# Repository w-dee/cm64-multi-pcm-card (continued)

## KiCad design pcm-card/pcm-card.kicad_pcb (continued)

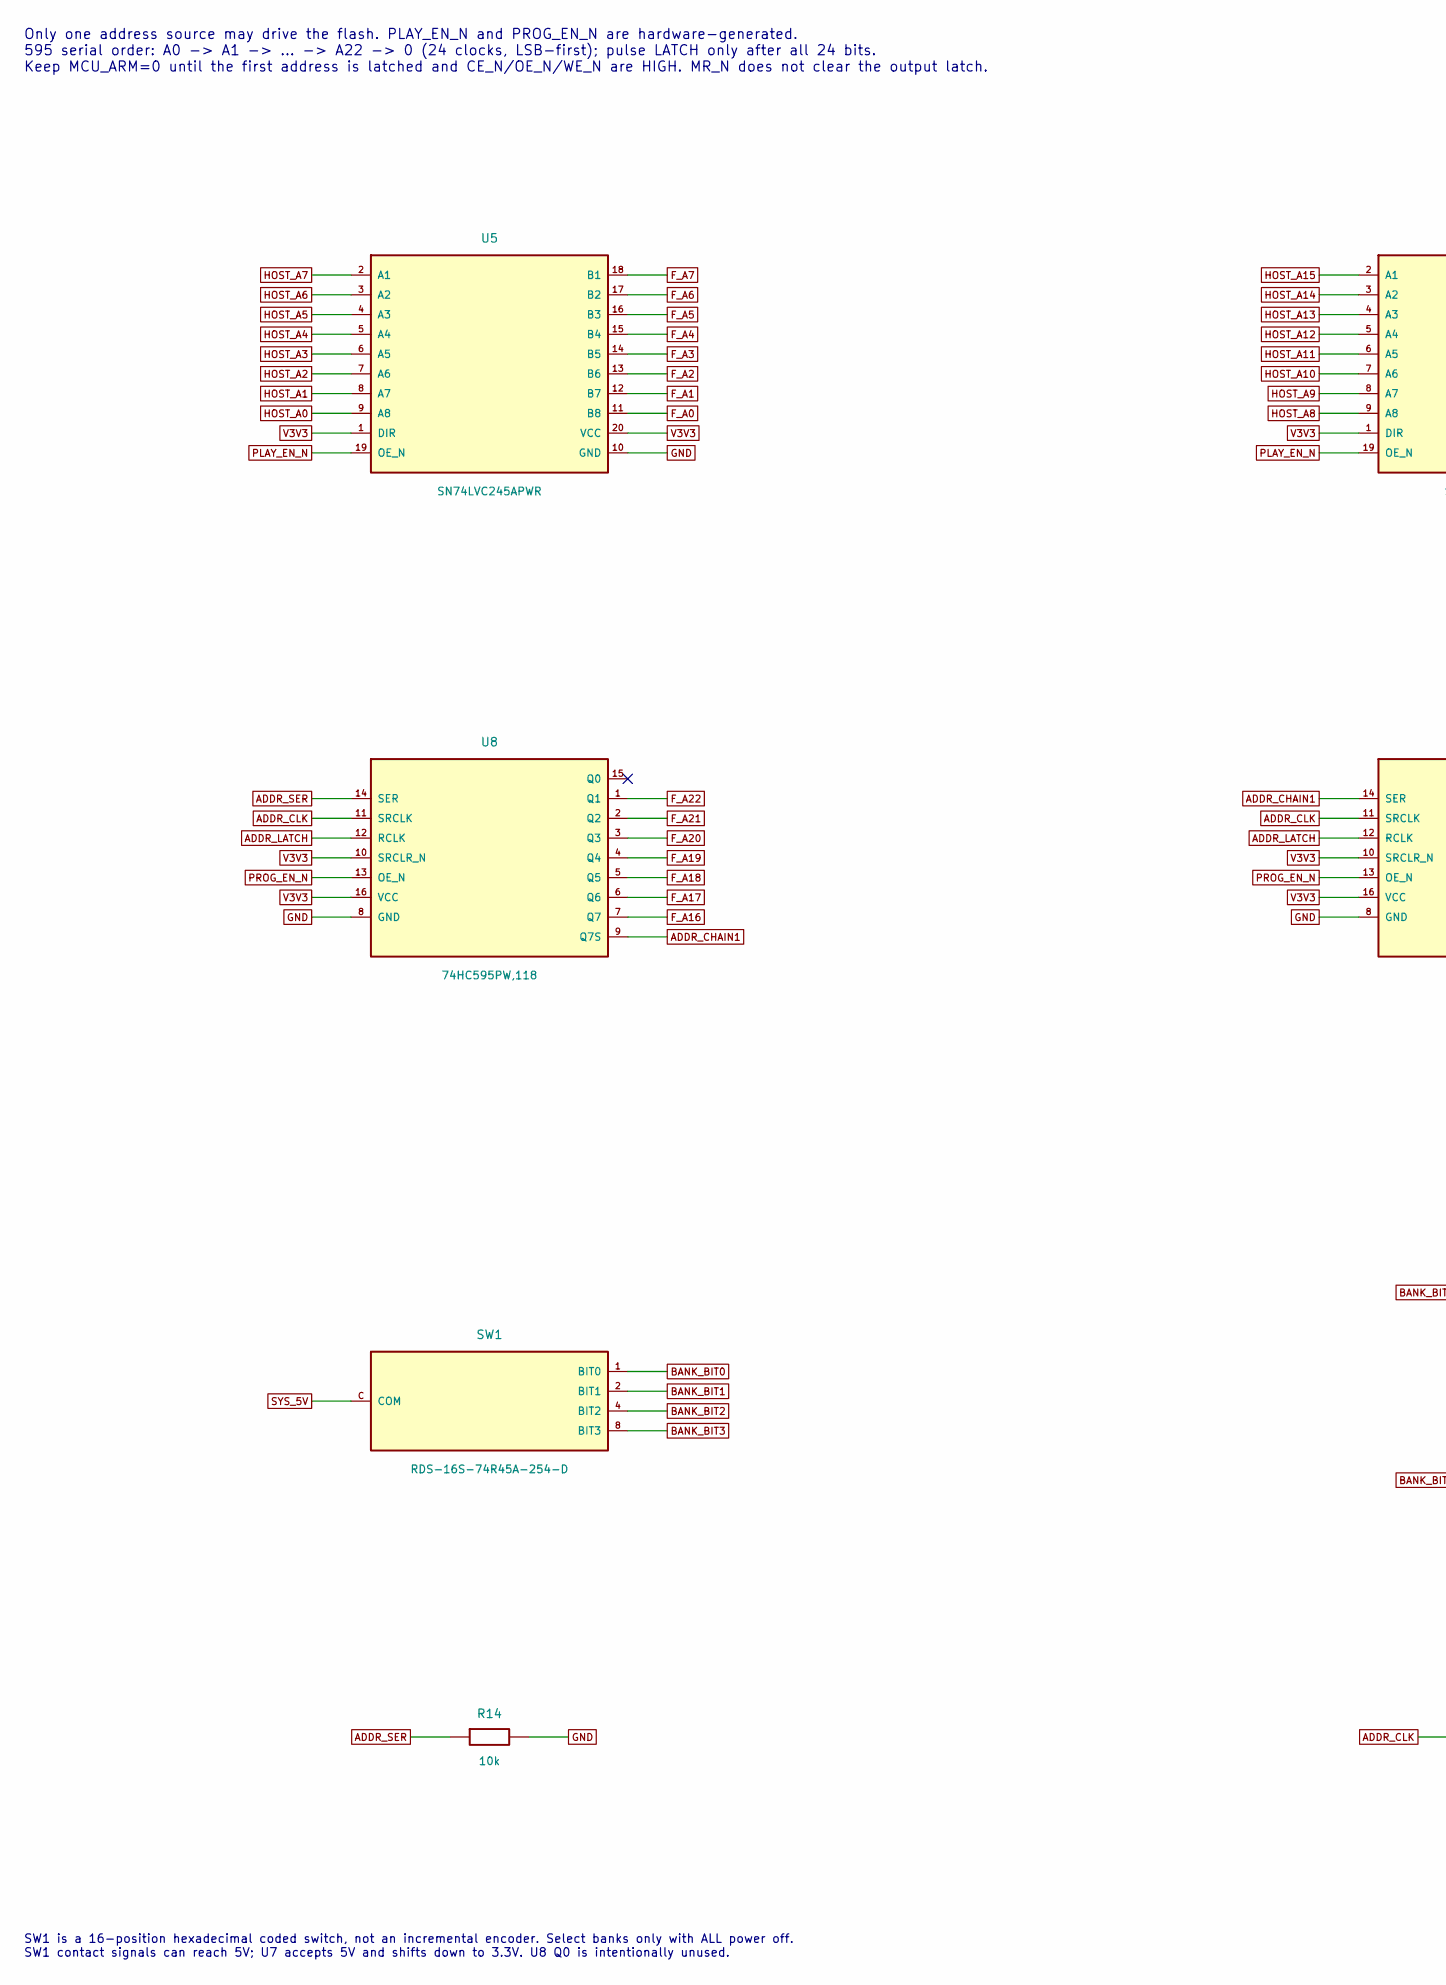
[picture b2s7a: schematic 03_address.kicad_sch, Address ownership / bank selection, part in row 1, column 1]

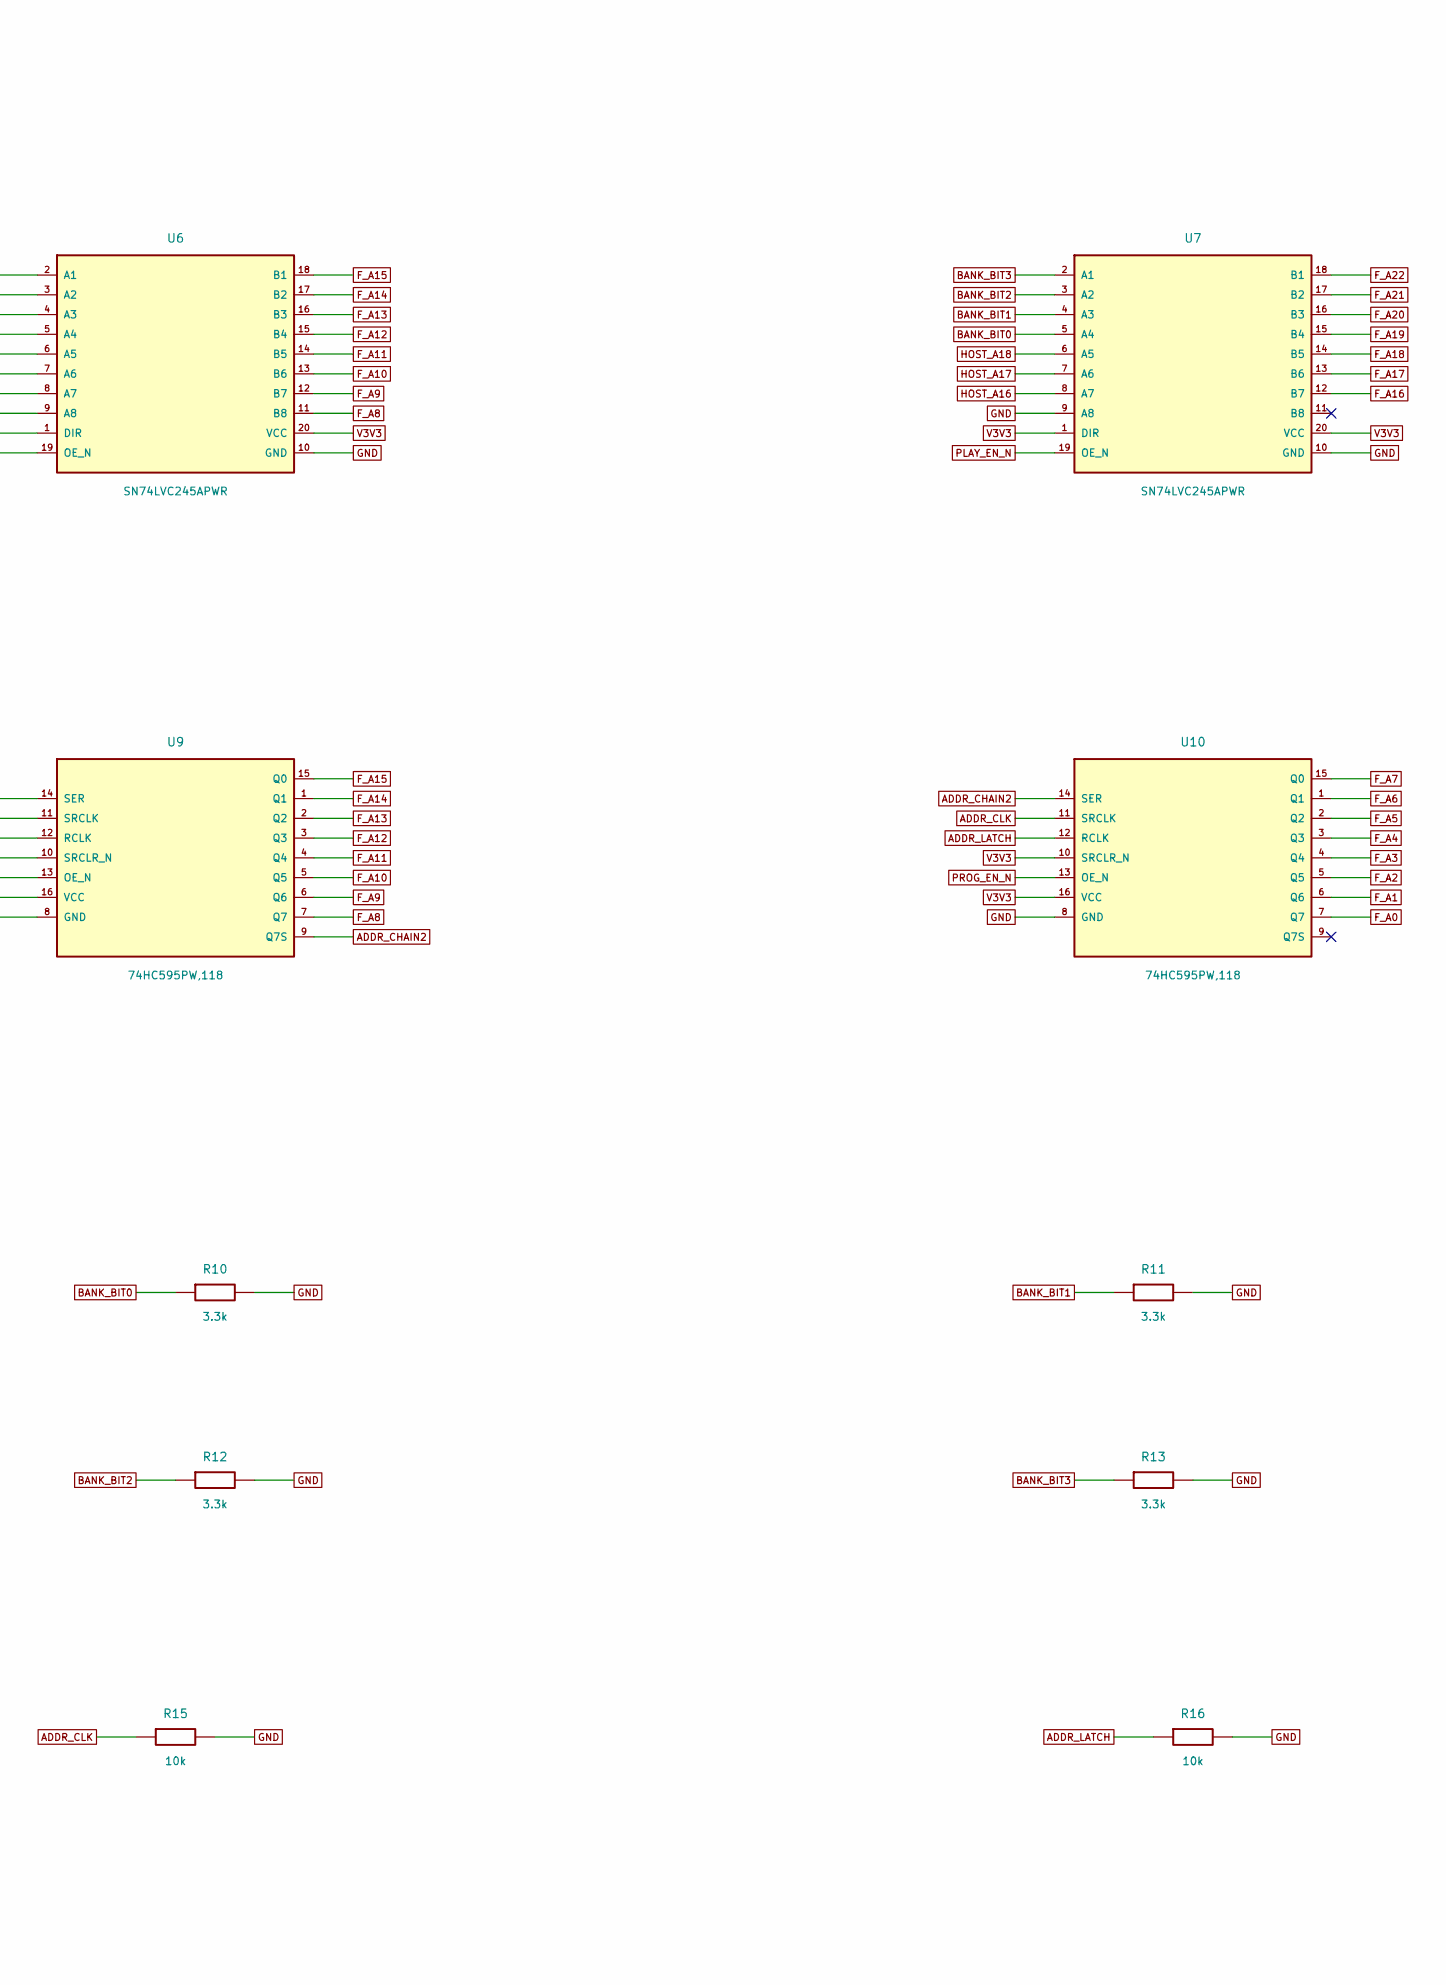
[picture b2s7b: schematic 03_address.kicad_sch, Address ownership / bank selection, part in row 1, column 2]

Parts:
R10, R11, R12, R13: 3.3k; R_0603_1608Metric; MPN 0603WAF3301T5E; LCSC C22978
R14, R15, R16: 10k; R_0603_1608Metric; MPN 0603WAF1002T5E; LCSC C25804
SW1: RDS-16S-74R45A-254-D; SameSky_RDS-16S-74R45A-254-D_THT; MPN RDS-16S-74R45A-254-D
U5, U6, U7: SN74LVC245APWR; TSSOP-20_4.4x6.5_P0.65; MPN SN74LVC245APWR; LCSC C7848
U8, U9, U10: 74HC595PW,118; TSSOP-16_4.4x5_P0.65; MPN 74HC595PW,118; LCSC C5948

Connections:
ADDR_CHAIN1: U8.9 (Q7S), U9.14 (SER)
ADDR_CHAIN2: U9.9 (Q7S), U10.14 (SER)
ADDR_CLK: R15.1, U8.11 (SRCLK), U9.11 (SRCLK), U10.11 (SRCLK); also elsewhere on the board
ADDR_LATCH: R16.1, U8.12 (RCLK), U9.12 (RCLK), U10.12 (RCLK); also elsewhere on the board
ADDR_SER: R14.1, U8.14 (SER); also elsewhere on the board
BANK_BIT0: R10.1, SW1.1 (BIT0), U7.5 (A4)
BANK_BIT1: R11.1, SW1.2 (BIT1), U7.4 (A3)
BANK_BIT2: R12.1, SW1.4 (BIT2), U7.3 (A2)
BANK_BIT3: R13.1, SW1.8 (BIT3), U7.2 (A1)
F_A0: U5.11 (B8), U10.7 (Q7); also elsewhere on the board
F_A1: U5.12 (B7), U10.6 (Q6); also elsewhere on the board
F_A2: U5.13 (B6), U10.5 (Q5); also elsewhere on the board
F_A3: U5.14 (B5), U10.4 (Q4); also elsewhere on the board
F_A4: U5.15 (B4), U10.3 (Q3); also elsewhere on the board
F_A5: U5.16 (B3), U10.2 (Q2); also elsewhere on the board
F_A6: U5.17 (B2), U10.1 (Q1); also elsewhere on the board
F_A7: U5.18 (B1), U10.15 (Q0); also elsewhere on the board
F_A8: U6.11 (B8), U9.7 (Q7); also elsewhere on the board
F_A9: U6.12 (B7), U9.6 (Q6); also elsewhere on the board
F_A10: U6.13 (B6), U9.5 (Q5); also elsewhere on the board
F_A11: U6.14 (B5), U9.4 (Q4); also elsewhere on the board
F_A12: U6.15 (B4), U9.3 (Q3); also elsewhere on the board
F_A13: U6.16 (B3), U9.2 (Q2); also elsewhere on the board
F_A14: U6.17 (B2), U9.1 (Q1); also elsewhere on the board
F_A15: U6.18 (B1), U9.15 (Q0); also elsewhere on the board
F_A16: U7.12 (B7), U8.7 (Q7); also elsewhere on the board
F_A17: U7.13 (B6), U8.6 (Q6); also elsewhere on the board
F_A18: U7.14 (B5), U8.5 (Q5); also elsewhere on the board
F_A19: U7.15 (B4), U8.4 (Q4); also elsewhere on the board
F_A20: U7.16 (B3), U8.3 (Q3); also elsewhere on the board
F_A21: U7.17 (B2), U8.2 (Q2); also elsewhere on the board
F_A22: U7.18 (B1), U8.1 (Q1); also elsewhere on the board
GND: R10.2, R11.2, R12.2, R13.2, R14.2, R15.2, R16.2, U5.10 (GND), U6.10 (GND), U7.9 (A8), U7.10 (GND), U8.8 (GND), U9.8 (GND), U10.8 (GND); also elsewhere on the board
HOST_A0: U5.9 (A8); also elsewhere on the board
HOST_A1: U5.8 (A7); also elsewhere on the board
HOST_A2: U5.7 (A6); also elsewhere on the board
HOST_A3: U5.6 (A5); also elsewhere on the board
HOST_A4: U5.5 (A4); also elsewhere on the board
HOST_A5: U5.4 (A3); also elsewhere on the board
HOST_A6: U5.3 (A2); also elsewhere on the board
HOST_A7: U5.2 (A1); also elsewhere on the board
HOST_A8: U6.9 (A8); also elsewhere on the board
HOST_A9: U6.8 (A7); also elsewhere on the board
HOST_A10: U6.7 (A6); also elsewhere on the board
HOST_A11: U6.6 (A5); also elsewhere on the board
HOST_A12: U6.5 (A4); also elsewhere on the board
HOST_A13: U6.4 (A3); also elsewhere on the board
HOST_A14: U6.3 (A2); also elsewhere on the board
HOST_A15: U6.2 (A1); also elsewhere on the board
HOST_A16: U7.8 (A7); also elsewhere on the board
HOST_A17: U7.7 (A6); also elsewhere on the board
HOST_A18: U7.6 (A5); also elsewhere on the board
PLAY_EN_N: U5.19 (OE_N), U6.19 (OE_N), U7.19 (OE_N); also elsewhere on the board
PROG_EN_N: U8.13 (OE_N), U9.13 (OE_N), U10.13 (OE_N); also elsewhere on the board
SYS_5V: SW1.C (COM); also elsewhere on the board
V3V3: U5.1 (DIR), U5.20 (VCC), U6.1 (DIR), U6.20 (VCC), U7.1 (DIR), U7.20 (VCC), U8.10 (SRCLR_N), U8.16 (VCC), U9.10 (SRCLR_N), U9.16 (VCC), U10.10 (SRCLR_N), U10.16 (VCC); also elsewhere on the board

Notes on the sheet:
SW1 is a 16-position hexadecimal coded switch, not an incremental encoder. Select banks only with ALL power off. SW1 contact signals can reach 5V; U7 accepts 5V and shifts down to 3.3V. U8 Q0 is intentionally unused.
Only one address source may drive the flash. PLAY_EN_N and PROG_EN_N are hardware-generated. 595 serial order: A0 -> A1 -> ... -> A22 -> 0 (24 clocks, LSB-first); pulse LATCH only after all 24 bits. Keep MCU_ARM=0 until the first address is latched and CE_N/OE_N/WE_N are HIGH. MR_N does not clear t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

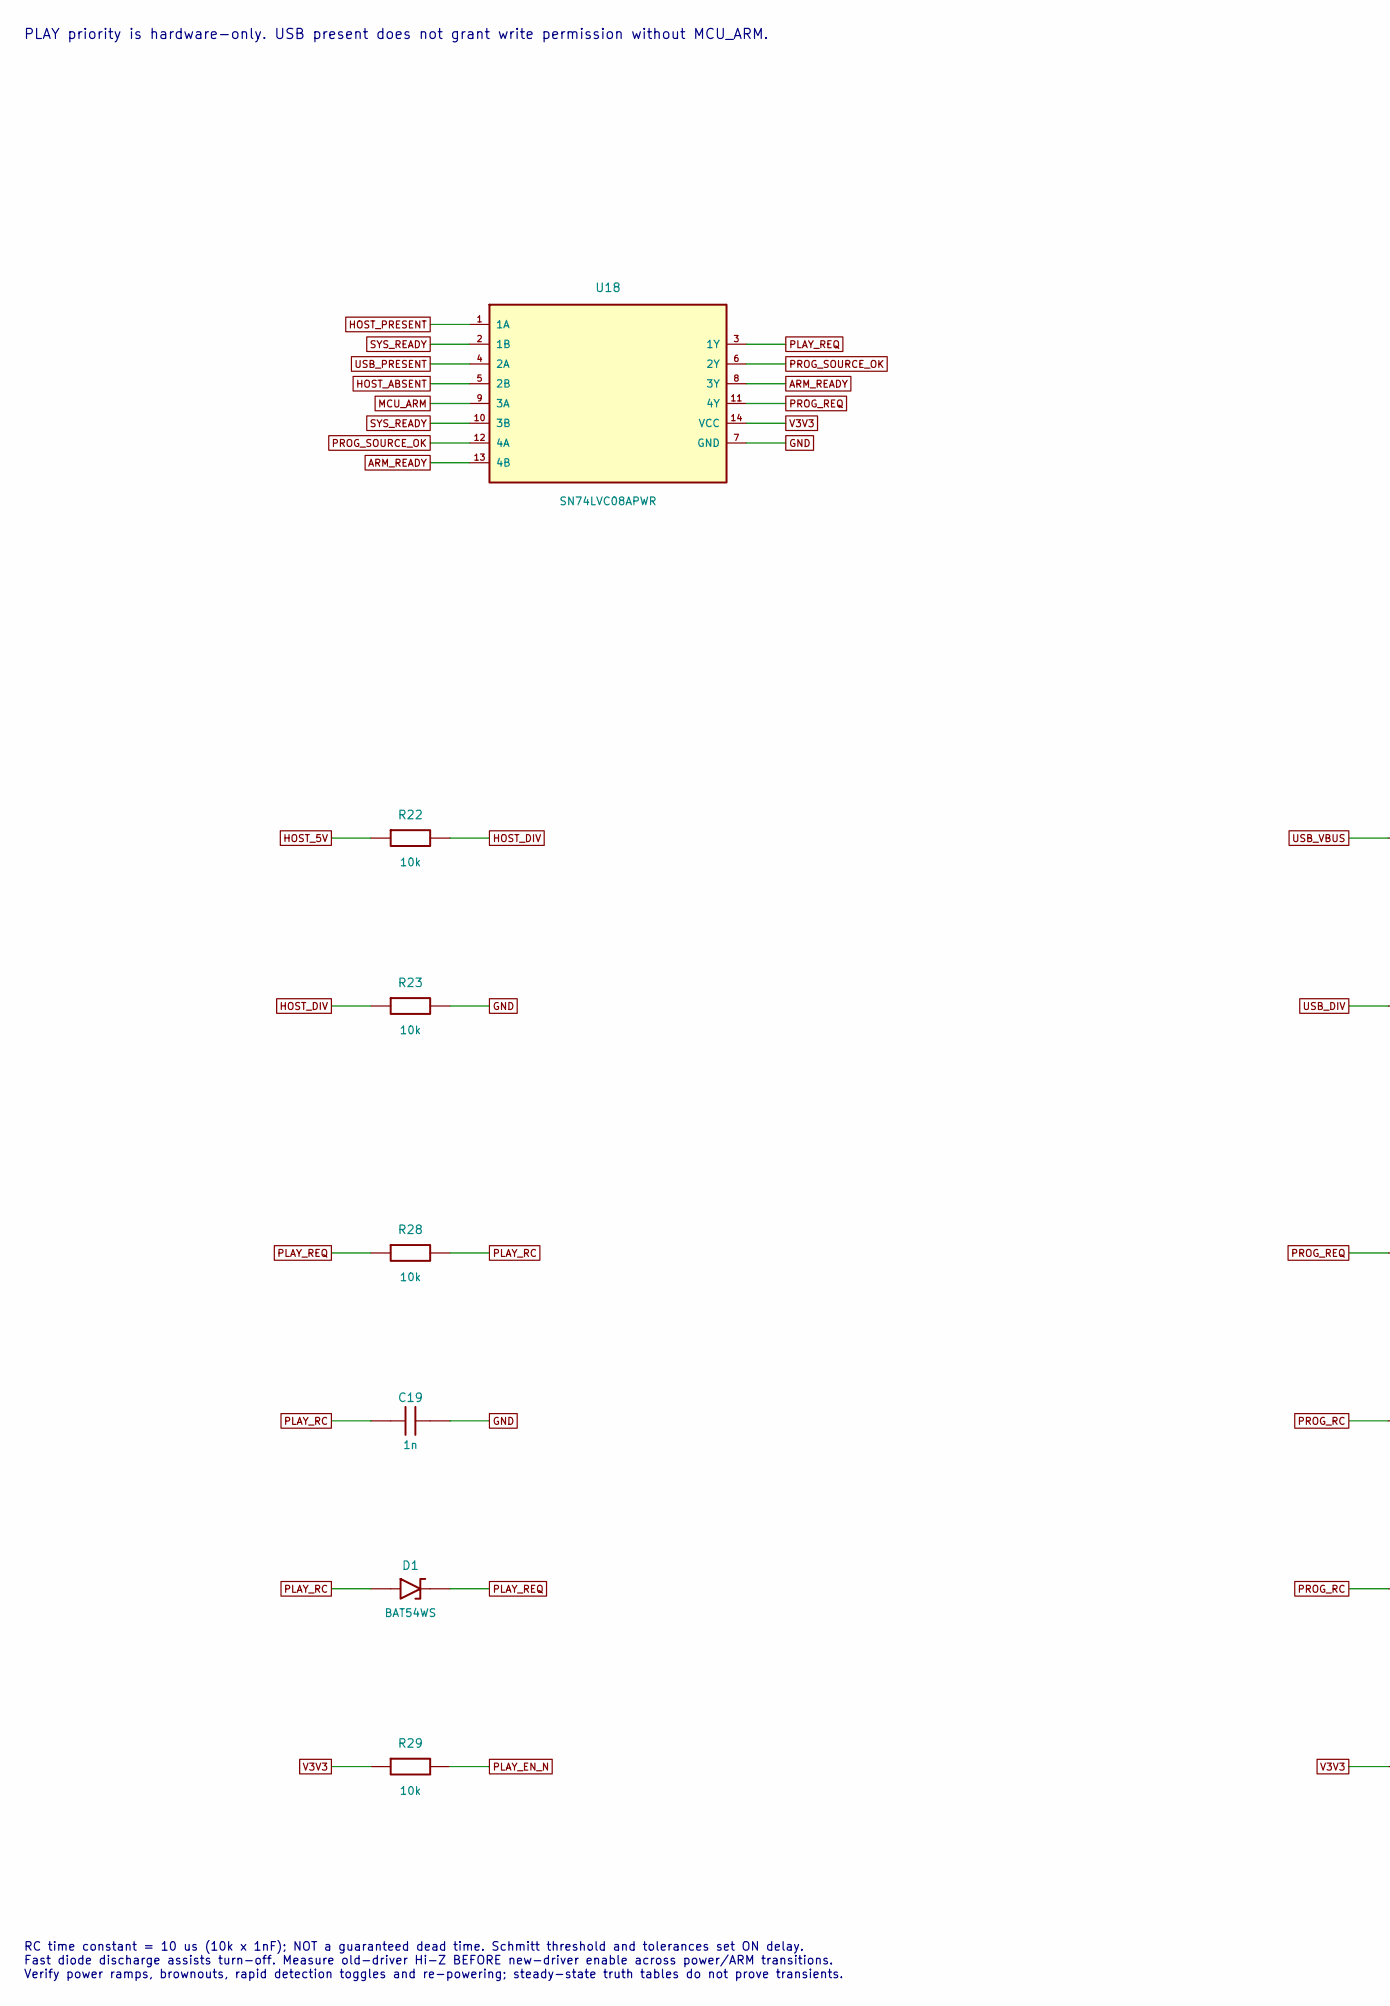
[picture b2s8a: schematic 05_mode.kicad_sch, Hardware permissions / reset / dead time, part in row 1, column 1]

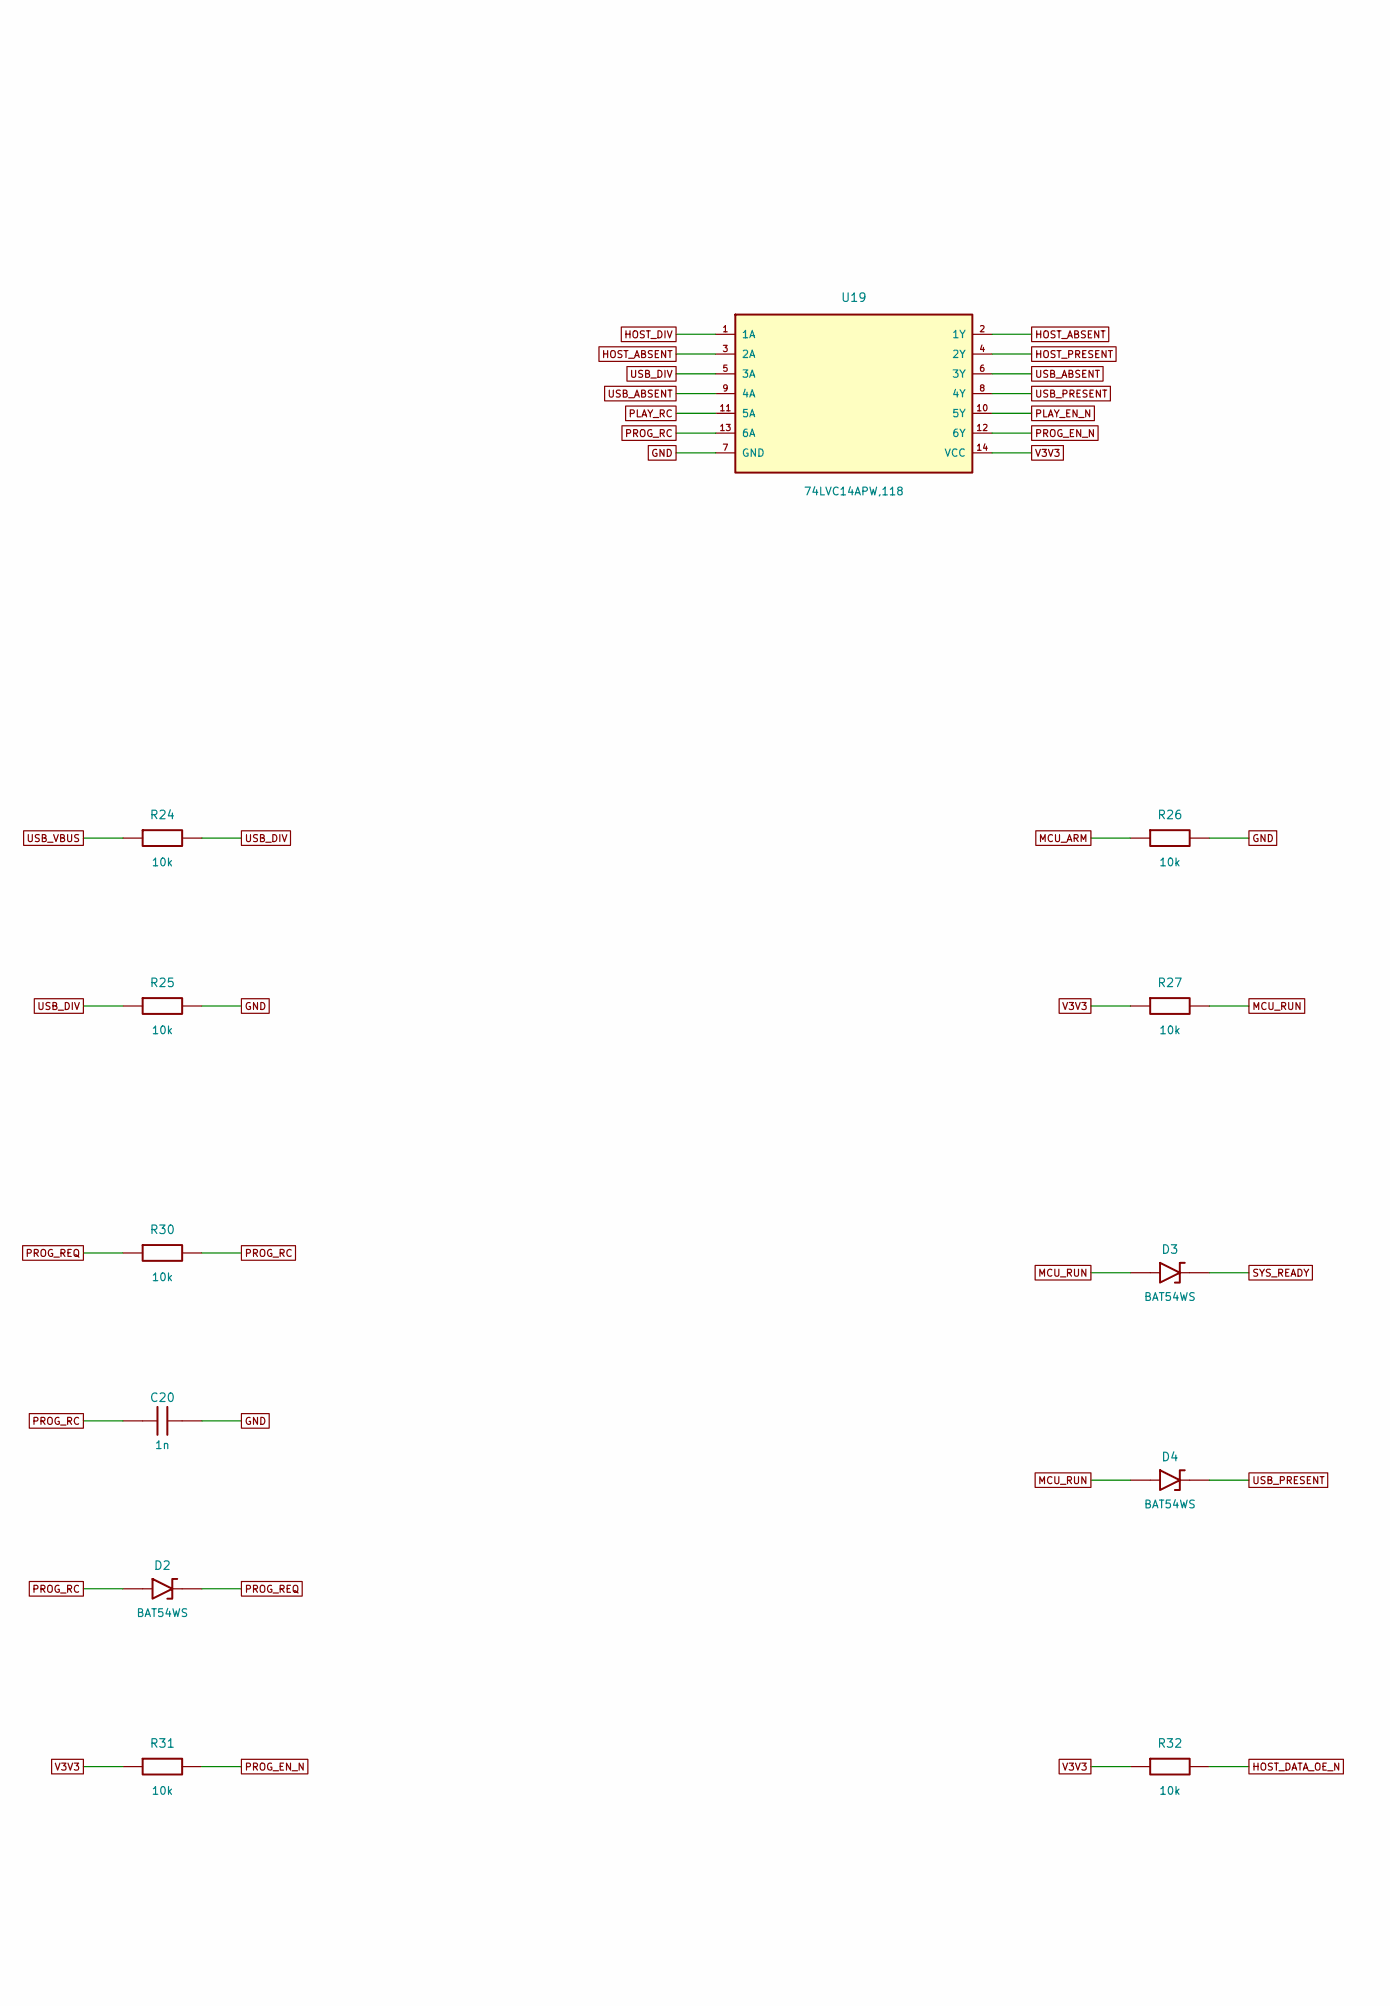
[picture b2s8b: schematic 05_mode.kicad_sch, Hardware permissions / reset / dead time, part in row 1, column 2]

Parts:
C19, C20: 1n; C_0603_1608Metric; MPN CL10B102KB8NNNC; LCSC C1588
D1, D2, D3, D4: BAT54WS; SOD-323; MPN BAT54WS; LCSC C438012
R22, R23, R24, R25, R26, R27, R28, R29, R30, R31, R32: 10k; R_0603_1608Metric; MPN 0603WAF1002T5E; LCSC C25804
U18: SN74LVC08APWR; TSSOP-14_4.4x5_P0.65; MPN SN74LVC08APWR; LCSC C465737
U19: 74LVC14APW,118; TSSOP-14_4.4x5_P0.65; MPN 74LVC14APW,118; LCSC C6066

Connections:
ARM_READY: U18.8 (3Y), U18.13 (4B)
GND: C19.2, C20.2, R23.2, R25.2, R26.2, U18.7 (GND), U19.7 (GND); also elsewhere on the board
HOST_5V: R22.1; also elsewhere on the board
HOST_ABSENT: U18.5 (2B), U19.2 (1Y), U19.3 (2A)
HOST_DATA_OE_N: R32.2; also elsewhere on the board
HOST_DIV: R22.2, R23.1, U19.1 (1A)
HOST_PRESENT: U18.1 (1A), U19.4 (2Y); also elsewhere on the board
MCU_ARM: R26.1, U18.9 (3A); also elsewhere on the board
MCU_RUN: D3.2, D4.2, R27.2; also elsewhere on the board
PLAY_EN_N: R29.2, U19.10 (5Y); also elsewhere on the board
PLAY_RC: C19.1, D1.2, R28.2, U19.11 (5A)
PLAY_REQ: D1.1, R28.1, U18.3 (1Y)
PROG_EN_N: R31.2, U19.12 (6Y); also elsewhere on the board
PROG_RC: C20.1, D2.2, R30.2, U19.13 (6A)
PROG_REQ: D2.1, R30.1, U18.11 (4Y)
PROG_SOURCE_OK: U18.6 (2Y), U18.12 (4A)
SYS_READY: D3.1, U18.2 (1B), U18.10 (3B); also elsewhere on the board
USB_ABSENT: U19.6 (3Y), U19.9 (4A)
USB_DIV: R24.2, R25.1, U19.5 (3A)
USB_PRESENT: D4.1, U18.4 (2A), U19.8 (4Y); also elsewhere on the board
USB_VBUS: R24.1; also elsewhere on the board
V3V3: R27.1, R29.1, R31.1, R32.1, U18.14 (VCC), U19.14 (VCC); also elsewhere on the board

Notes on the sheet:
RC time constant = 10 us (10k x 1nF); NOT a guaranteed dead time. Schmitt threshold and tolerances set ON delay. Fast diode discharge assists turn-off. Measure old-driver Hi-Z BEFORE new-driver enable across power/ARM transitions. Verify power ramps, brownouts, rapid detection toggles and re-poweri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
PLAY priority is hardware-only. USB present does not grant write permission without MCU_ARM.

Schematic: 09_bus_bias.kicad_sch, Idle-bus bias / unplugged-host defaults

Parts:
R98: 100k; R_0603_1608Metric; MPN 0603WAF1003T5E; LCSC C25803
R99: 10k; R_0603_1608Metric; MPN 0603WAF1002T5E; LCSC C25804
RN1, RN2, RN3, RN4, RN5, RN6, RN7, RN8, RN9, RN10, RN11, RN12, RN13, RN14, RN15: 4x100k; Yageo_YC164_4x0603; Tolerance 1%; Power Rating 62.5mW per element; MPN YC164-FR-07100KL; LCSC C110374

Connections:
F_A0: RN6.4; also elsewhere on the board
F_A1: RN6.3; also elsewhere on the board
F_A2: RN6.2; also elsewhere on the board
F_A3: RN6.1; also elsewhere on the board
F_A4: RN7.4; also elsewhere on the board
F_A5: RN7.3; also elsewhere on the board
F_A6: RN7.2; also elsewhere on the board
F_A7: RN7.1; also elsewhere on the board
F_A8: RN8.4; also elsewhere on the board
F_A9: RN8.3; also elsewhere on the board
F_A10: RN8.2; also elsewhere on the board
F_A11: RN8.1; also elsewhere on the board
F_A12: RN9.4; also elsewhere on the board
F_A13: RN9.3; also elsewhere on the board
F_A14: RN9.2; also elsewhere on the board
F_A15: RN9.1; also elsewhere on the board
F_A16: RN10.4; also elsewhere on the board
F_A17: RN10.3; also elsewhere on the board
F_A18: RN10.2; also elsewhere on the board
F_A19: RN10.1; also elsewhere on the board
F_A20: RN11.3; also elsewhere on the board
F_A21: RN11.2; also elsewhere on the board
F_A22: RN11.1; also elsewhere on the board
F_D0: RN12.4; also elsewhere on the board
F_D1: RN12.3; also elsewhere on the board
F_D2: RN12.2; also elsewhere on the board
F_D3: RN12.1; also elsewhere on the board
F_D4: RN13.4; also elsewhere on the board
F_D5: RN13.3; also elsewhere on the board
F_D6: RN13.2; also elsewhere on the board
F_D7: RN13.1; also elsewhere on the board
GND: RN1.5, RN1.6, RN1.7, RN1.8, RN2.5, RN2.6, RN2.7, RN2.8, RN3.5, RN3.6, RN3.7, RN3.8, RN4.5, RN4.6, RN4.7, RN4.8, RN5.5, RN5.6, RN5.7, RN5.8, RN6.5, RN6.6, RN6.7, RN6.8, RN7.5, RN7.6, RN7.7, RN7.8, RN8.5, RN8.6, RN8.7, RN8.8, RN9.5, RN9.6, RN9.7, RN9.8, RN10.5, RN10.6, RN10.7, RN10.8, RN11.5, RN11.6, RN11.7, RN12.5, RN12.6, RN12.7, RN12.8, RN13.5, RN13.6, RN13.7, RN13.8, RN14.5, RN14.6, RN14.7, RN14.8, RN15.5, RN15.6, RN15.7, RN15.8; also elsewhere on the board
HOST_5V: R98.1; also elsewhere on the board
HOST_A0: RN1.4; also elsewhere on the board
HOST_A1: RN1.3; also elsewhere on the board
HOST_A2: RN1.2; also elsewhere on the board
HOST_A3: RN1.1; also elsewhere on the board
HOST_A4: RN2.4; also elsewhere on the board
HOST_A5: RN2.3; also elsewhere on the board
HOST_A6: RN2.2; also elsewhere on the board
HOST_A7: RN2.1; also elsewhere on the board
HOST_A8: RN3.4; also elsewhere on the board
HOST_A9: RN3.3; also elsewhere on the board
HOST_A10: RN3.2; also elsewhere on the board
HOST_A11: RN3.1; also elsewhere on the board
HOST_A12: RN4.4; also elsewhere on the board
HOST_A13: RN4.3; also elsewhere on the board
HOST_A14: RN4.2; also elsewhere on the board
HOST_A15: RN4.1; also elsewhere on the board
HOST_A16: RN5.4; also elsewhere on the board
HOST_A17: RN5.3; also elsewhere on the board
HOST_A18: RN5.2; also elsewhere on the board
HOST_CS: RN5.1; also elsewhere on the board
HOST_OE_N: R98.2; also elsewhere on the board
MCU_BUF_OE_N: R99.2; also elsewhere on the board
MCU_D0: RN15.4; also elsewhere on the board
MCU_D1: RN15.3; also elsewhere on the board
MCU_D2: RN15.2; also elsewhere on the board
MCU_D3: RN15.1; also elsewhere on the board
MCU_D4: RN14.4; also elsewhere on the board
MCU_D5: RN14.3; also elsewhere on the board
MCU_D6: RN14.2; also elsewhere on the board
MCU_D7: RN14.1; also elsewhere on the board
V3V3: R99.1; also elsewhere on the board

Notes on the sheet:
59 bus pull-downs: RN1..RN15, 4x100k isolated arrays (YAGEO YC164-FR-07100KL / C110374).
Pin pairs: 1-5, 2-6, 3-7, 4-8. RN11 pins 4 and 8 are spare / NC. R98 remains a HOST_5V pull-up. 100k loads: 50uA at 5V, 33uA at 3.3V. Do not substitute a common-pin resistor network.

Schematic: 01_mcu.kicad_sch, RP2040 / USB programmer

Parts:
C2, C3: 15p; C_0603_1608Metric; MPN CL10C150JB8NNNC; LCSC C1644
D5: Green; LED_0603_1608Metric; MPN KT-0603G; LCSC C12624
D6: Red; LED_0603_1608Metric; MPN KT-0603R; LCSC C2286
J2: BOOTSEL; SolderJumper-2_P1.3mm_Open_RoundedPad1.0x1.5mm; MPN TSW-102-07-G-S
R1, R5, R100, R101: 1k; R_0603_1608Metric; MPN 0603WAF1001T5E; LCSC C21190
R2, R103, R104, R105, R106: 10k; R_0603_1608Metric; MPN 0603WAF1002T5E; LCSC C25804
R3, R4: 27; R_0603_1608Metric; MPN 0603WAF270JT5E; LCSC C25190
R102, R107: 100k; R_0603_1608Metric; MPN 0603WAF1003T5E; LCSC C25803
U2: W25Q128JVPIQ; WSON-8_6x5mm_P1.27mm_EP3.4x4.3mm_Floating; MPN W25Q128JVPIQ; LCSC C190862
U3: RP2040; QFN-56-1EP_7x7_P0.4_EP3.2; MPN RP2040; LCSC C2040
X1: 12MHz CL=10pF; Crystal_3225_4pad; MPN ABM8-272-T3; LCSC C20625731

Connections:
ADDR_CLK: U3.28 (GPIO17); also elsewhere on the board
ADDR_LATCH: U3.29 (GPIO18); also elsewhere on the board
ADDR_SER: U3.27 (GPIO16); also elsewhere on the board
BOOTSEL_N: J2.1, R1.2
FLASH_RY_BY_N: R102.1; also elsewhere on the board
GND: C2.2, C3.2, D5.1 (K), D6.1 (K), J2.2, U2.4 (GND), U3.19 (TESTEN), U3.57 (GND_EP), X1.2 (GND_2), X1.4 (GND_4); also elsewhere on the board
HOST_PRESENT: R103.1; also elsewhere on the board
LED_GREEN: R100.1, U3.30 (GPIO19)
LED_GREEN_A: D5.2 (A), R100.2
LED_RED: R101.1, U3.31 (GPIO20)
LED_RED_A: D6.2 (A), R101.2
MCU_ARM: U3.16 (GPIO13); also elsewhere on the board
MCU_CE_N: U3.13 (GPIO10); also elsewhere on the board
MCU_D0: U3.2 (GPIO0); also elsewhere on the board
MCU_D1: U3.3 (GPIO1); also elsewhere on the board
MCU_D2: U3.4 (GPIO2); also elsewhere on the board
MCU_D3: U3.5 (GPIO3); also elsewhere on the board
MCU_D4: U3.6 (GPIO4); also elsewhere on the board
MCU_D5: U3.7 (GPIO5); also elsewhere on the board
MCU_D6: U3.8 (GPIO6); also elsewhere on the board
MCU_D7: U3.9 (GPIO7); also elsewhere on the board
MCU_DATA_DIR: U3.11 (GPIO8); also elsewhere on the board
MCU_DATA_OE_N: U3.12 (GPIO9); also elsewhere on the board
MCU_OE_N: U3.14 (GPIO11); also elsewhere on the board
MCU_RUN: U3.26 (RUN); also elsewhere on the board
MCU_WE_N: U3.15 (GPIO12); also elsewhere on the board
MON_HOST_PRESENT: R103.2, U3.18 (GPIO15)
MON_PROG_EN_N: R106.2, U3.38 (GPIO26)
MON_RY_BY_N: R102.2, U3.17 (GPIO14)
MON_SYS_READY: R105.2, U3.36 (GPIO24)
MON_USB_FAULT_N: R107.2, U3.39 (GPIO27)
MON_USB_PRESENT: R104.2, U3.35 (GPIO23)
PROG_EN_N: R106.1; also elsewhere on the board
QSPI_CLK: U2.6 (CLK), U3.52 (QSPI_SCLK)
QSPI_CS_N: R1.1, R2.2, U2.1 (CS_N), U3.56 (QSPI_SS_N)
QSPI_D0: U2.5 (IO0), U3.53 (QSPI_SD0)
QSPI_D1: U2.2 (IO1), U3.55 (QSPI_SD1)
QSPI_D2: U2.3 (IO2_WP_N), U3.54 (QSPI_SD2)
QSPI_D3: U2.7 (IO3_HOLD_N), U3.51 (QSPI_SD3)
SWCLK: U3.24 (SWCLK); also elsewhere on the board
SWDIO: U3.25 (SWDIO); also elsewhere on the board
SYS_READY: R105.1; also elsewhere on the board
USB_DM_MCU: R4.2, U3.46 (USB_DM)
USB_DM_PORT: R4.1; also elsewhere on the board
USB_DP_MCU: R3.2, U3.47 (USB_DP)
USB_DP_PORT: R3.1; also elsewhere on the board
USB_FAULT_N: R107.1; also elsewhere on the board
USB_PRESENT: R104.1; also elsewhere on the board
V3V3: R2.1, U2.8 (VCC), U3.1 (IOVDD_1), U3.10 (IOVDD_10), U3.22 (IOVDD_22), U3.33 (IOVDD_33), U3.42 (IOVDD_42), U3.43 (ADC_AVDD), U3.44 (VREG_IN), U3.48 (USB_VDD), U3.49 (IOVDD_49); also elsewhere on the board
VREG_1V1: U3.23 (DVDD_23), U3.45 (VREG_VOUT), U3.50 (DVDD_50); also elsewhere on the board
XIN: C2.1, U3.20 (XIN), X1.1 (XTAL1)
XOUT: R5.1, U3.21 (XOUT)
XTAL_OUT: C3.1, R5.2, X1.3 (XTAL2)

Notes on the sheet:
USB-only programming: remove the card from CM-64. Start with ARM=0, DATA_OE_N=1 and all strobes HIGH. Load all 24 address bits before ARM=1. Wait >=100 us after arming. Deassert ARM before USB disconnect.
GPIO0..7=data; GPIO16/17/18=595 serial/clock/latch. Firmware is not in the PLAY path.
Status LEDs: GPIO19=green, GPIO20=red. HIGH=ON; LOW=OFF. Each LED uses 1k in series.
Monitor GPIOs: input, pulls OFF, Schmitt ON. 100k on open-drain status; 10k on push-pull control.

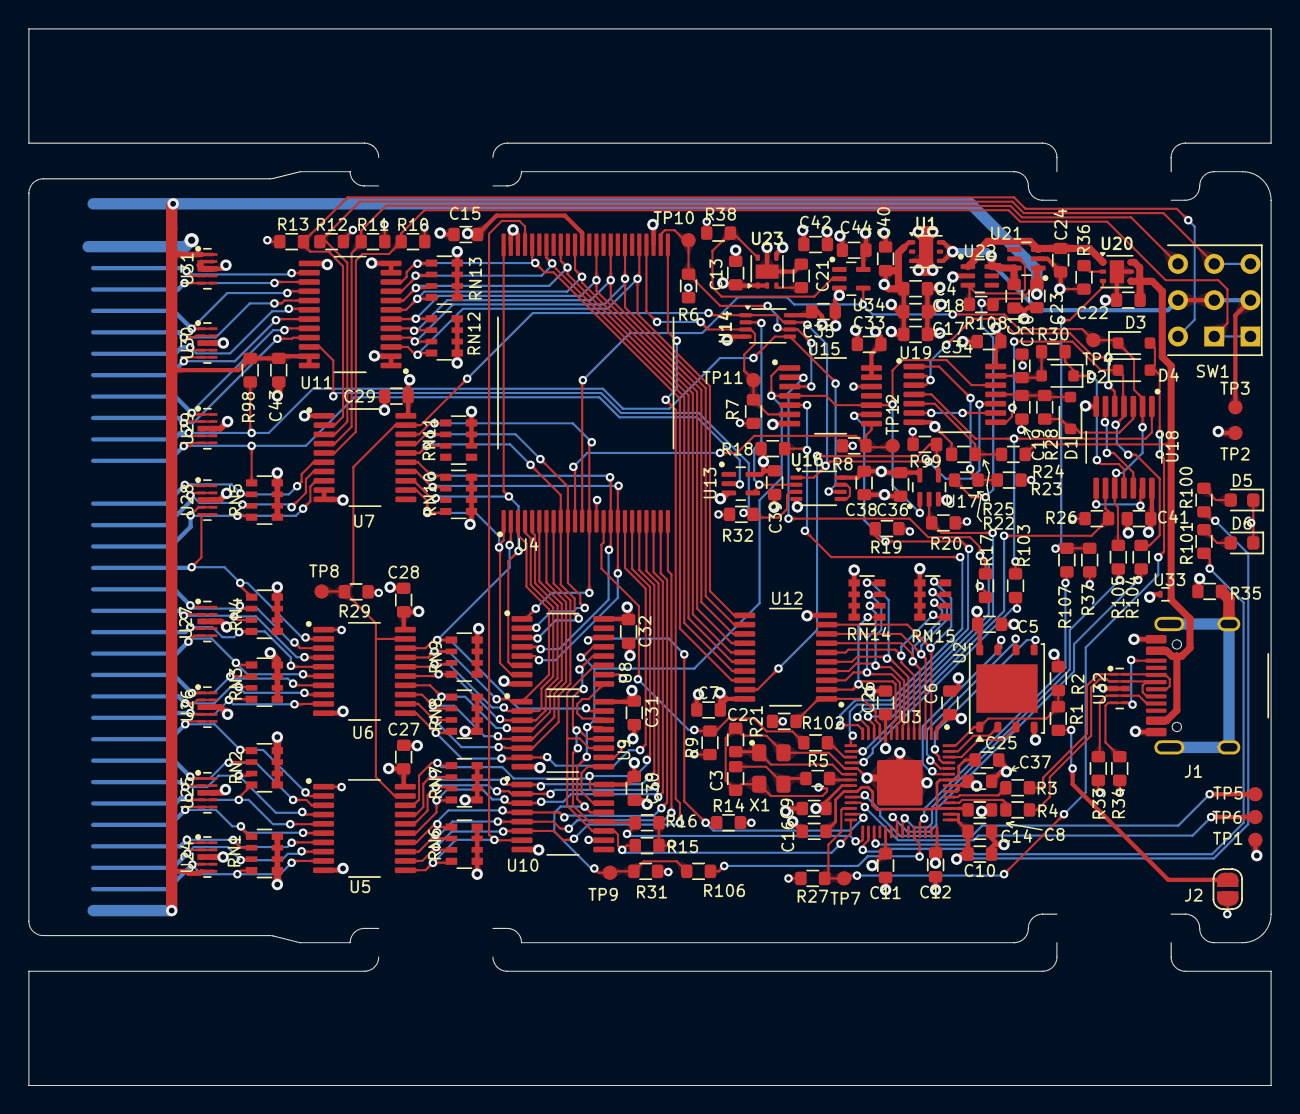
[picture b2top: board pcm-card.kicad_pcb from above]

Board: 4 copper layers, 87.0 x 74.0 mm, 165 parts (1 on the bottom side), 148 nets.
